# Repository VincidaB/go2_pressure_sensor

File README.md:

The pressure sensor used is the GZP6859A040KPP33Z, as a replacement for the original XGZP6869A040 (Both have a pressure range between 0-40KPa).

The tube on the GO2 EDU is 1mm ID and 3mm OD silicone tubing, but I could make it fit on the pressure sensors, so I used 1.5mm ID instead. A small piece of tape or heat shrink can be used ont the foot side to make it fit better.

The screws needed are M2 length 4mm countersunk screws, the original being Philips head. 7 screws are needed per leg, for a total of 28 screws. They fix the tubing using two small plastic brackets than can be 3D printed, the files are in the `3d_models` folder (4 of each must be printed).

By removing a plastic cover on the inner part of the leg, a connector is revealed, which connects to the sensor once it has been fastened : 

One of the 3D printed brackets, fastened, holding the tube in place:

Here is the final PCBs manufactured and assembled:

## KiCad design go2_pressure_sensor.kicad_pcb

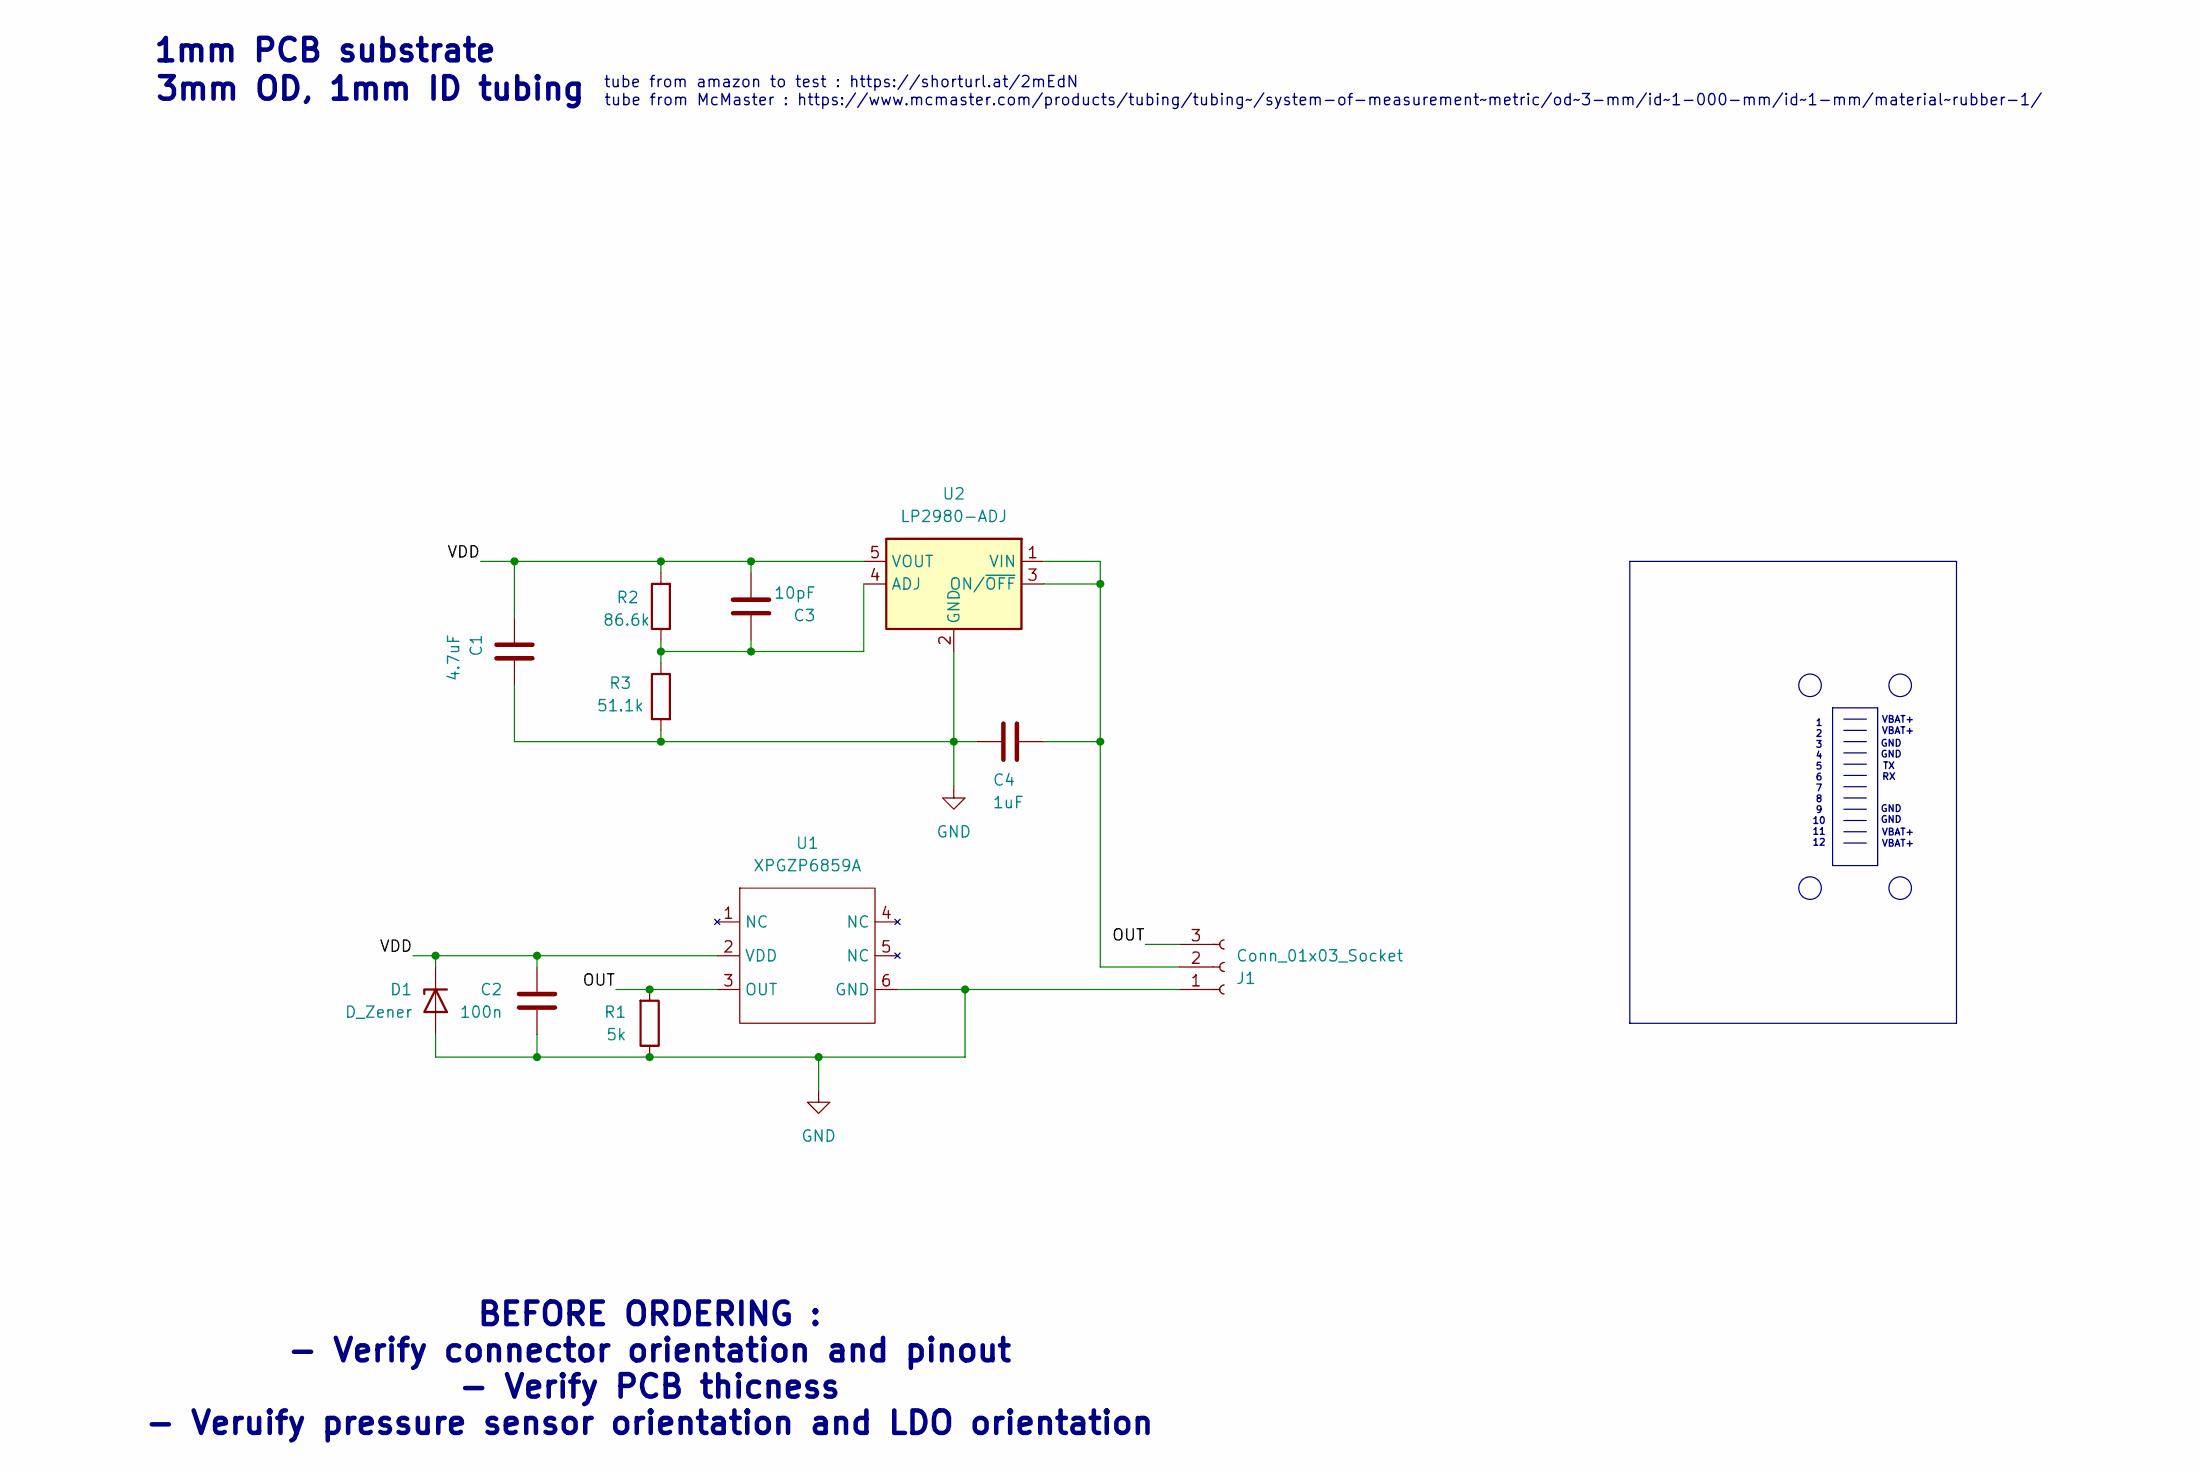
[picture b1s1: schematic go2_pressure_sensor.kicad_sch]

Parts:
C1: 4.7uF; R_0603_1608Metric; LCSC C19666
C2: 100n; C_0603_1608Metric; LCSC C66501
C3: 10pF; R_0603_1608Metric; LCSC C106245
C4: 1uF; R_0603_1608Metric; LCSC C6119849
D1: D_Zener; D_SOD-123; LCSC C2117
J1: Conn_01x03_Socket; JST_GH_BM03B-GHS-TBT_1x03-1MP_P1.25mm_Vertical; LCSC C161691
R1: 5k; R_0603_1608Metric; LCSC C2828621
R2: 86.6k; R_0603_1608Metric; LCSC C3000725
R3: 51.1k; R_0603_1608Metric; LCSC C2933234
U1: XPGZP6859A; XGZ6859 6pin; LCSC C3038019
U2: LP2980-ADJ; SOT-23-5; LCSC C181526

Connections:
/OUT: J1.3, R1.2, U1.3 (OUT)
/VDD: C1.2, C2.1, C3.1, D1.1 (K), R2.2, U1.2 (VDD), U2.5 (VOUT)
GND: C1.1, C2.2, C4.2, D1.2 (A), J1.1, R1.1, R3.2, U1.6 (GND), U2.2 (GND)
unnamed: C4.1, J1.2, U2.1 (VIN), U2.3 (ON/~OFF)
unnamed: C3.2, R2.1, R3.1, U2.4 (ADJ)

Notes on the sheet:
GND GND
BEFORE ORDERING : - Verify connector orientation and pinout - Verify PCB thicness - Veruify pressure sensor orientation and LDO orientation
1 2 3 4 5 6 7 8 9 10 11 12
1mm PCB substrate
VBAT+
3mm OD, 1mm ID tubing
tube from amazon to test : https://shorturl.at/2mEdN
tube from McMaster : https://www.mcmaster.com/products/tubing/tubing~/system-of-measurement~metric/od~3-mm/id~1-000-mm/id~1-mm/material~rubber-1/
TX RX

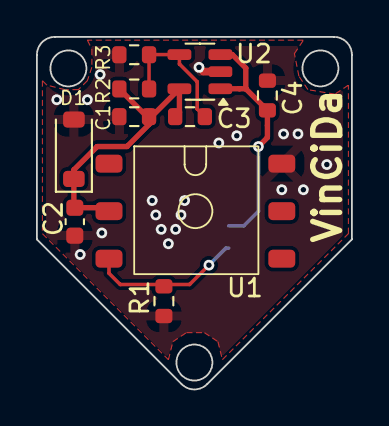
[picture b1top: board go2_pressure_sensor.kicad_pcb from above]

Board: 2 copper layers, 17.5 x 19.6 mm, 11 parts (1 on the bottom side), 5 nets.

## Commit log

2024-10-30 init git repo
2024-10-30 Added datasheets for the potential and the current sensors
2024-10-30 Added LDO datasheet
2024-10-30 Added connector diagram of the GO2 battery (unrelated)
2024-10-31 Non verified version with new presure transducer
2024-11-01 Backlink to CADLAB.io has been added.
2024-11-01 Removed copied sensors schematic
2024-11-25 removed step model
2024-11-25 Added silkscreen markings for pressure sensor
2025-01-10 Update README.md to add pressure sensor part number
2025-01-17 Added more details to README
2025-01-17 Added more images
2026-02-01 Added thumbnail image
